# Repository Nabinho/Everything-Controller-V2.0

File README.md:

# Everything Controller V2.0

This project is an updated version of my Everything Controller I did a while back. This time I focused on transmission time, using the powerfull Teensy 3.2 as the main microcontroller. I also added more inputs, so I have even more functions to help the control of various projects, and not only robots.

The PCB and base code of this project are available for replication. The Teensy 3.2 is discontinued, so if you don't have one, maybe this can be a great reference for your own project.

## BOM

The SMD components list can be found in the interactive BOM generated with the KiCad project. Besides the Teensy 3.2 I had for a while, the rest of the THT components I bought from Aliexpress and all of the links are listed below.

* 1x - [EByte E01](https://pt.aliexpress.com/item/1005001803228202.html?spm=a2g0o.order_list.order_list_main.110.3876caa4MgzPN5&gatewayAdapt=glo2bra);
* 1x - [Waveshare SSD1327 128x128 OLED Display](https://pt.aliexpress.com/item/32853228170.html?spm=a2g0o.order_list.order_list_main.22.3876caa4MgzPN5&gatewayAdapt=glo2bra);
* 2x - [10k Ohm Rotary Potentiometer](https://pt.aliexpress.com/item/1005005956593595.html?spm=a2g0o.order_list.order_list_main.34.3876caa4MgzPN5&gatewayAdapt=glo2bra);
* 2x - [10k Ohm Slider Potentiometer](https://pt.aliexpress.com/item/1005006075347058.html?spm=a2g0o.order_list.order_list_main.35.3876caa4MgzPN5&gatewayAdapt=glo2bra);
* 2x - [EC11 Rotary Encoder](https://pt.aliexpress.com/item/1005005882895811.html?spm=a2g0o.order_list.order_list_main.36.3876caa4MgzPN5&gatewayAdapt=glo2bra);
* 4x - [Cherry MX Switches (any color)](https://pt.aliexpress.com/item/1005006255961111.html?spm=a2g0o.cart.0.0.360c7f06wTXtF8&mp=1&gatewayAdapt=glo2bra);
* 2x - [PS5 Hall Effect Joystick](https://pt.aliexpress.com/item/1005006165745072.html?spm=a2g0o.order_list.order_list_main.58.3876caa4MgzPN5&gatewayAdapt=glo2bra);

Besides the electronics components, a pair of 18650 Li-Ion batteries is necessary to power the controller.

Some screws and nuts ares also recommended to mount the soldered PCB in an acrylic or 3D printed backplate.

## Bechmark Tests

As soon as the controller was finished I ran some benchmark tests to validate the controller performance. Bellow are the tests I ran so far and the results.

| Tests | Results |
| ------------- |:-------------:|
| Battery feedback reading | The battery feedback circuit from the controller had a precision of 0.3 mV most of the time, but I had to include a "debounce" for the OLED update, due to some voltage fluctuation |
| Transmission latency | With a simple receiver just connected to the NRF24L01 transceiver and only calculating the time between messages (data sent and acknolegement) the average time was 3 ms during an 1 hour test |
| Battery duration | Using a pair of 3000 mAh 18650 Li-Ion batteries the controller stayed turned on during 21 hours (average consumption of 150 mA) |
| Transmission range | This test is still TBD, however I want to see if the optimistic expectations from EByte of a transmission range of 5 km is true |

### Conclusion/Contact

As this is a personal project, I would love to see if anyone replicate or takes inspiration from this project. So if you replicate or use this as a base for your own project, please share it with me in Instagram.

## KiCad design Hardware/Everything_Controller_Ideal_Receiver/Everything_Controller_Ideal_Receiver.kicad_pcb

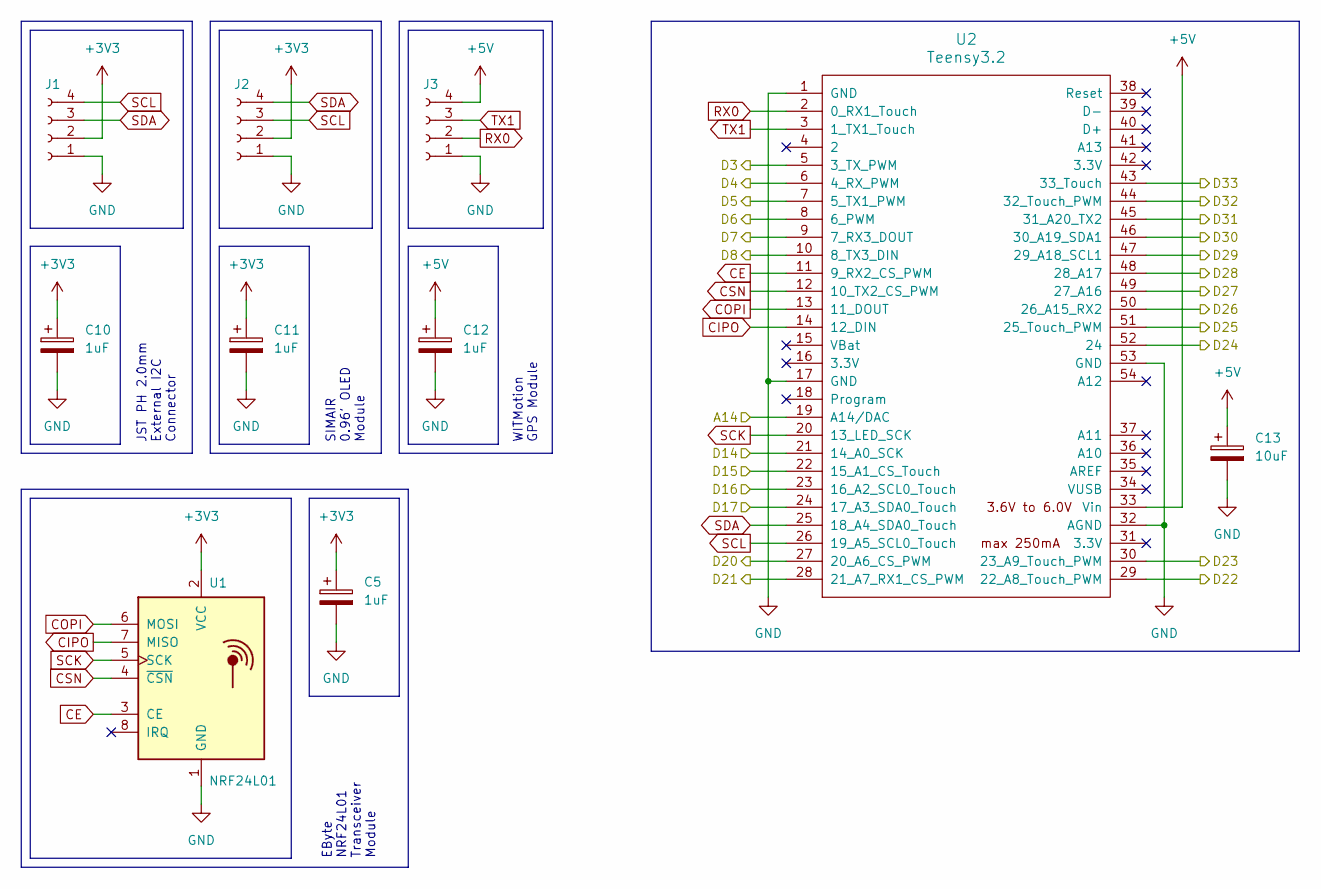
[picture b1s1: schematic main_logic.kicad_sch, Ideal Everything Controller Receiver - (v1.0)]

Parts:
C5, C10, C11, C12: 1uF; CP_EIA-3216-18_Kemet-A
C13: 10uF; CP_EIA-3528-21_Kemet-B
J1: Conn_01x04_Socket; JST_PH_S4B-PH-K_1x04_P2.00mm_Horizontal
J2: Conn_01x04_Socket; SIMAIR_OLED
J3: Conn_01x04_Socket; WitMotion_NMEA0183
U1: NRF24L01; EByte_NRF24L01_Breakout
U2: Teensy3.2; Teensy_3.2

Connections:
+3V3: C5.1, C10.1, C11.1, J1.2, J2.2, U1.2 (VCC); also elsewhere on the board
+5V: C12.1, C13.1, J3.4, U2.33 (Vin); also elsewhere on the board
/Inputs and Outputs/BOTAO1: U2.21 (14_A0_SCK); also elsewhere on the board
/Inputs and Outputs/BOTAO2: U2.22 (15_A1_CS_Touch); also elsewhere on the board
/Inputs and Outputs/BOTAO3: U2.23 (16_A2_SCL0_Touch); also elsewhere on the board
/Inputs and Outputs/BOTAO4: U2.24 (17_A3_SDA0_Touch); also elsewhere on the board
/Inputs and Outputs/DOUT1: U2.47 (29_A18_SCL1); also elsewhere on the board
/Inputs and Outputs/DOUT2: U2.46 (30_A19_SDA1); also elsewhere on the board
/Inputs and Outputs/DOUT3: U2.45 (31_A20_TX2); also elsewhere on the board
/Inputs and Outputs/DOUT4: U2.48 (28_A17); also elsewhere on the board
/Inputs and Outputs/DOUT5: U2.49 (27_A16); also elsewhere on the board
/Inputs and Outputs/DOUT6: U2.50 (26_A15_RX2); also elsewhere on the board
/Inputs and Outputs/DOUT7: U2.51 (25_Touch_PWM); also elsewhere on the board
/Inputs and Outputs/DOUT8: U2.52 (24); also elsewhere on the board
/Inputs and Outputs/LED1: U2.44 (32_Touch_PWM); also elsewhere on the board
/Inputs and Outputs/LED2: U2.43 (33_Touch); also elsewhere on the board
/Inputs and Outputs/PPM1: U2.29 (22_A8_Touch_PWM); also elsewhere on the board
/Inputs and Outputs/PPM2: U2.30 (23_A9_Touch_PWM); also elsewhere on the board
/Inputs and Outputs/PWM1: U2.10 (8_TX3_DIN); also elsewhere on the board
/Inputs and Outputs/PWM2: U2.9 (7_RX3_DOUT); also elsewhere on the board
/Inputs and Outputs/PWM3: U2.8 (6_PWM); also elsewhere on the board
/Inputs and Outputs/PWM4: U2.7 (5_TX1_PWM); also elsewhere on the board
/Inputs and Outputs/PWM5: U2.6 (4_RX_PWM); also elsewhere on the board
/Inputs and Outputs/PWM6: U2.5 (3_TX_PWM); also elsewhere on the board
/Inputs and Outputs/PWM7: U2.27 (20_A6_CS_PWM); also elsewhere on the board
/Inputs and Outputs/PWM8: U2.28 (21_A7_RX1_CS_PWM); also elsewhere on the board
/Main Logic/A14: U2.19 (A14/DAC); also elsewhere on the board
CE: U1.3 (CE), U2.11 (9_RX2_CS_PWM)
CIPO: U1.7 (MISO), U2.14 (12_DIN)
COPI: U1.6 (MOSI), U2.13 (11_DOUT)
CSN: U1.4 (~CSN), U2.12 (10_TX2_CS_PWM)
GND: C5.2, C10.2, C11.2, C12.2, C13.2, J1.1, J2.1, J3.1, U1.1 (GND), U2.1 (GND), U2.17 (GND), U2.32 (AGND), U2.53 (GND); also elsewhere on the board
RX0: J3.2, U2.2 (0_RX1_Touch)
SCK: U1.5 (SCK), U2.20 (13_LED_SCK)
SCL: J1.4, J2.3, U2.26 (19_A5_SCL0_Touch)
SDA: J1.3, J2.4, U2.25 (18_A4_SDA0_Touch)
TX1: J3.3, U2.3 (1_TX1_Touch)

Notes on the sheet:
SIMAIR 0.96' OLED Module
WITMotion GPS Module
JST PH 2.0mm External I2C Connector
EByte NRF24L01 Transceiver Module

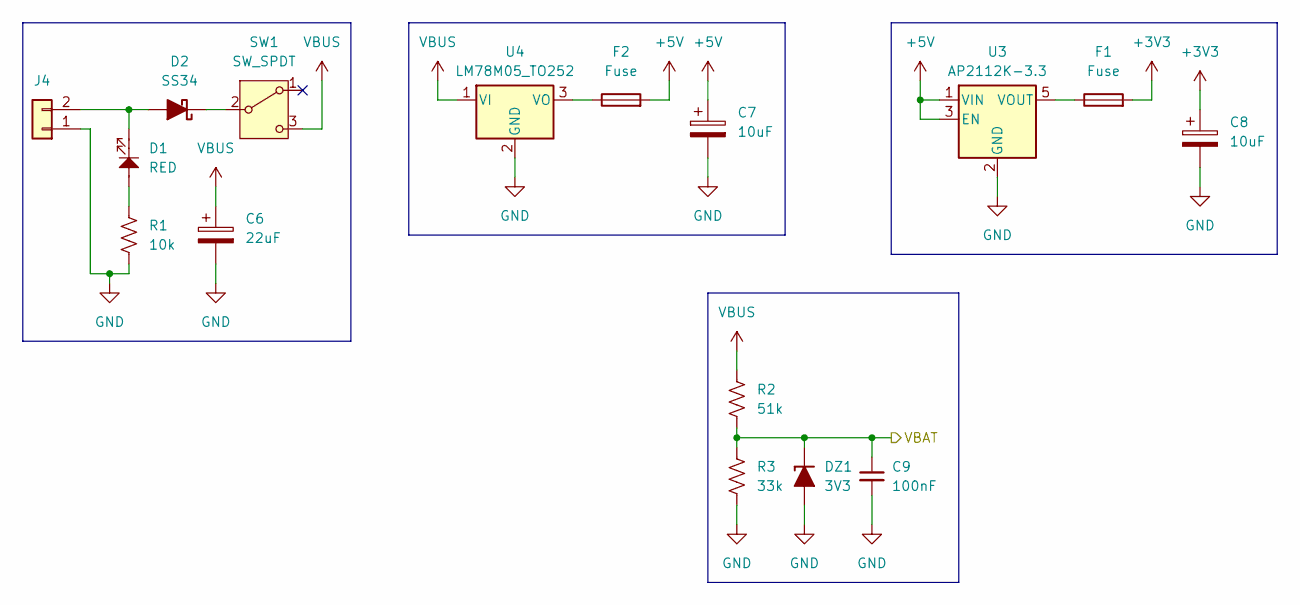
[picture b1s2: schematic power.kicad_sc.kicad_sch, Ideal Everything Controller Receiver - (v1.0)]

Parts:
C6: 22uF; CP_EIA-7343-31_Kemet-D
C7, C8: 10uF; CP_EIA-3528-21_Kemet-B
C9: 100nF; C_0805_2012Metric
D1: RED; LED_0805_2012Metric
D2: SS34; D_SMA
DZ1: 3V3; D_MiniMELF
F1: Fuse; Fuse_0805_2012Metric
F2: Fuse; Fuse_1812_4532Metric
J4: Conn_01x02; TerminalBlock_4Ucon_1x02_P3.50mm_Horizontal
R1: 10k; R_0805_2012Metric
R2: 51k; R_0805_2012Metric
R3: 33k; R_0805_2012Metric
SW1: SW_SPDT; SW_Slide_SPDT_Straight_CK_OS102011MS2Q
U3: AP2112K-3.3; SOT-23-5
U4: LM78M05_TO252; TO-252-2

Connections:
+3V3: C8.1, F1.2; also elsewhere on the board
+5V: C7.1, F2.2, U3.1 (VIN), U3.3 (EN); also elsewhere on the board
/Main Logic/A14: C9.1, DZ1.1 (K), R2.2, R3.1; also elsewhere on the board
GND: C6.2, C7.2, C8.2, C9.2, DZ1.2 (A), J4.1, R1.2, R3.2, U3.2 (GND), U4.2 (GND); also elsewhere on the board
unnamed: D1.2, R1.1
unnamed: D1.1, D2.2 (A), J4.2
unnamed: D2.1 (K), SW1.2 (B)
unnamed: F1.1, U3.5 (VOUT)
unnamed: F2.1, U4.3 (VO)
VBUS: C6.1, R2.1, SW1.3 (C), U4.1 (VI)

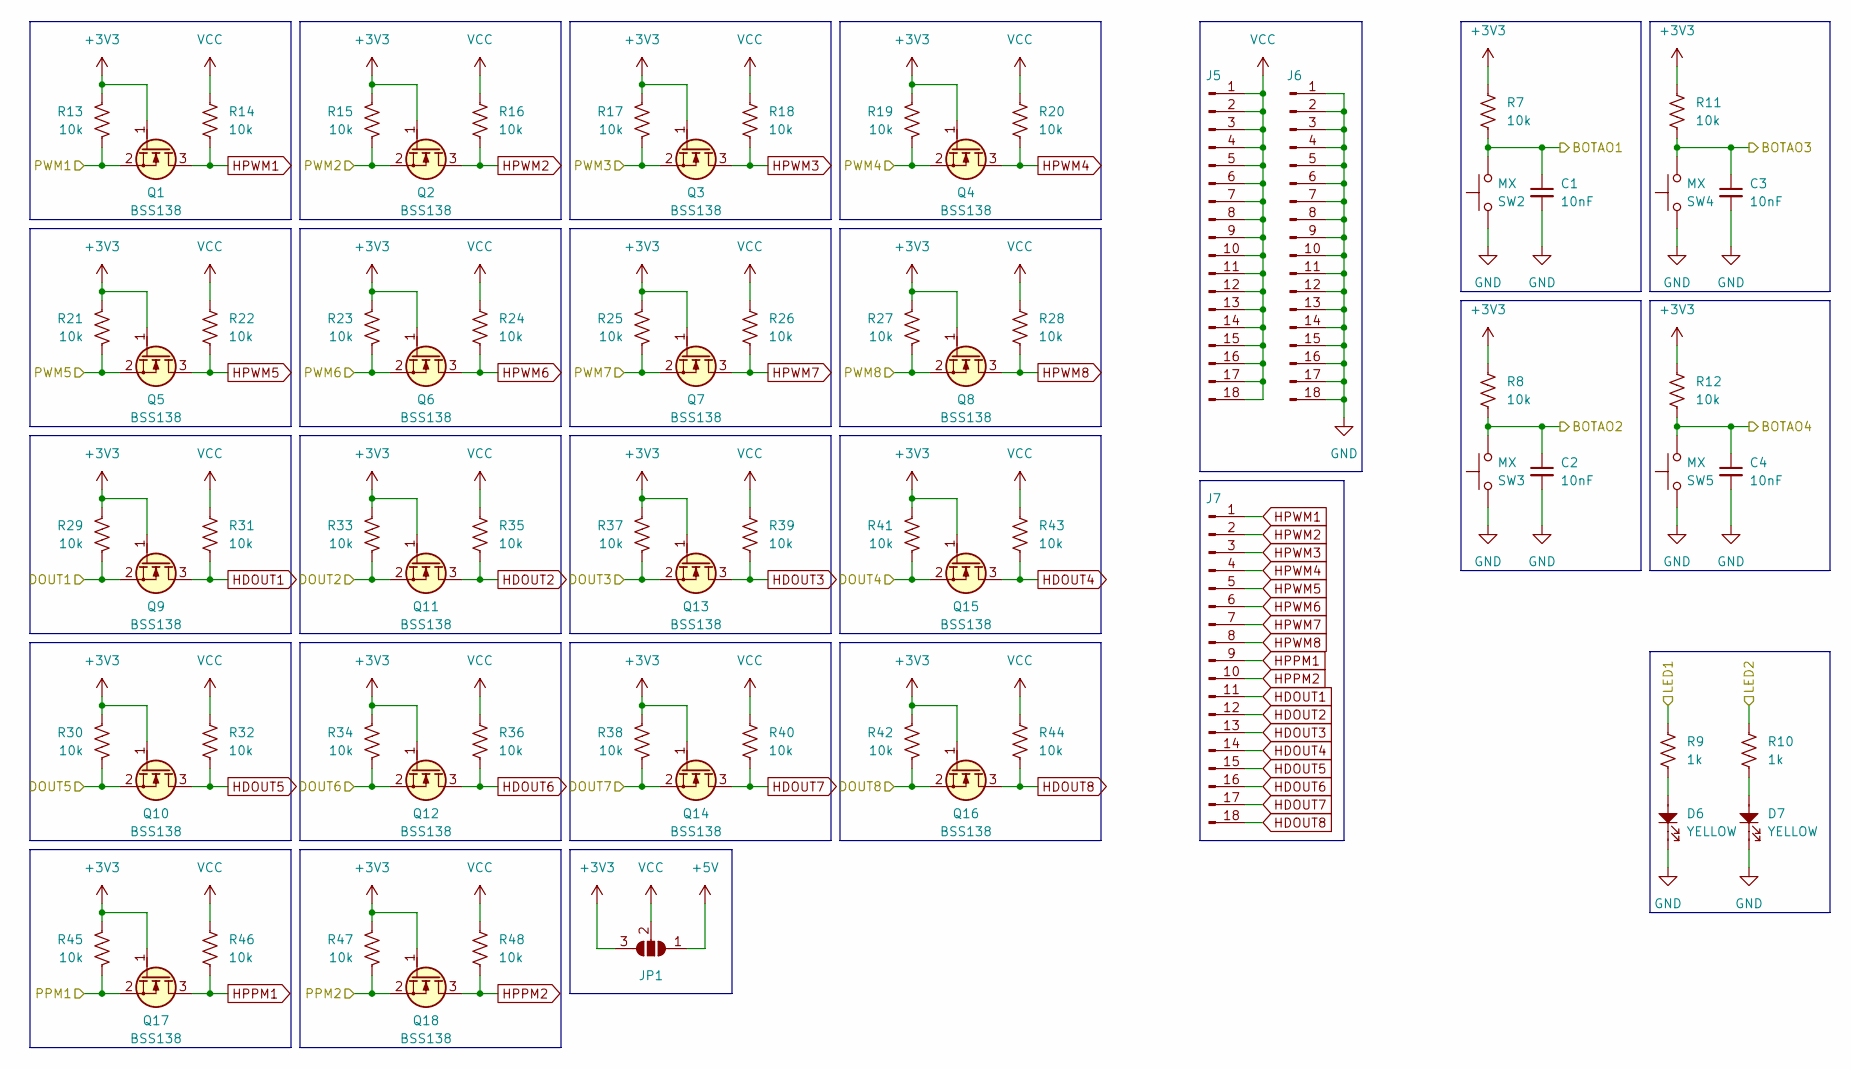
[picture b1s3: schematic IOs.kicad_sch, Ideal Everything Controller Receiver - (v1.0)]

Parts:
C1, C2, C3, C4: 10nF; C_0805_2012Metric
D6, D7: YELLOW; LED_0805_2012Metric
J5, J6, J7: Conn_01x18_Pin; PinHeader_1x18_P2.54mm_Vertical
JP1: SolderJumper_3_Open; SolderJumper-3_P1.3mm_Open_RoundedPad1.0x1.5mm
Q1, Q2, Q3, Q4, Q5, Q6, Q7, Q8, Q9, Q10, Q11, Q12, Q13, Q14, Q15, Q16, Q17, Q18: BSS138; SOT-23
R7, R8, R11, R12, R13, R14, R15, R16, R17, R18, R19, R20, R21, R22, R23, R24, R25, R26, R27, R28, R29, R30, R31, R32, R33, R34, R35, R36, R37, R38, R39, R40, R41, R42, R43, R44, R45, R46, R47, R48: 10k; R_0805_2012Metric
R9, R10: 1k; R_0805_2012Metric
SW2, SW3, SW4, SW5: MX; SW_Cherry_MX_PCB_1.00u

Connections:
+3V3: JP1.3 (B), Q1.1 (G), Q2.1 (G), Q3.1 (G), Q4.1 (G), Q5.1 (G), Q6.1 (G), Q7.1 (G), Q8.1 (G), Q9.1 (G), Q10.1 (G), Q11.1 (G), Q12.1 (G), Q13.1 (G), Q14.1 (G), Q15.1 (G), Q16.1 (G), Q17.1 (G), Q18.1 (G), R7.1, R8.1, R11.1, R12.1, R13.1, R15.1, R17.1, R19.1, R21.1, R23.1, R25.1, R27.1, R29.1, R30.1, R33.1, R34.1, R37.1, R38.1, R41.1, R42.1, R45.1, R47.1; also elsewhere on the board
+5V: JP1.1 (A); also elsewhere on the board
/Inputs and Outputs/BOTAO1: C1.1, R7.2, SW2.1; also elsewhere on the board
/Inputs and Outputs/BOTAO2: C2.1, R8.2, SW3.1; also elsewhere on the board
/Inputs and Outputs/BOTAO3: C3.1, R11.2, SW4.1; also elsewhere on the board
/Inputs and Outputs/BOTAO4: C4.1, R12.2, SW5.1; also elsewhere on the board
/Inputs and Outputs/DOUT1: Q9.2 (S), R29.2; also elsewhere on the board
/Inputs and Outputs/DOUT2: Q11.2 (S), R33.2; also elsewhere on the board
/Inputs and Outputs/DOUT3: Q13.2 (S), R37.2; also elsewhere on the board
/Inputs and Outputs/DOUT4: Q15.2 (S), R41.2; also elsewhere on the board
/Inputs and Outputs/DOUT5: Q10.2 (S), R30.2; also elsewhere on the board
/Inputs and Outputs/DOUT6: Q12.2 (S), R34.2; also elsewhere on the board
/Inputs and Outputs/DOUT7: Q14.2 (S), R38.2; also elsewhere on the board
/Inputs and Outputs/DOUT8: Q16.2 (S), R42.2; also elsewhere on the board
/Inputs and Outputs/LED1: R9.1; also elsewhere on the board
/Inputs and Outputs/LED2: R10.1; also elsewhere on the board
/Inputs and Outputs/PPM1: Q17.2 (S), R45.2; also elsewhere on the board
/Inputs and Outputs/PPM2: Q18.2 (S), R47.2; also elsewhere on the board
/Inputs and Outputs/PWM1: Q1.2 (S), R13.2; also elsewhere on the board
/Inputs and Outputs/PWM2: Q2.2 (S), R15.2; also elsewhere on the board
/Inputs and Outputs/PWM3: Q3.2 (S), R17.2; also elsewhere on the board
/Inputs and Outputs/PWM4: Q4.2 (S), R19.2; also elsewhere on the board
/Inputs and Outputs/PWM5: Q5.2 (S), R21.2; also elsewhere on the board
/Inputs and Outputs/PWM6: Q6.2 (S), R23.2; also elsewhere on the board
/Inputs and Outputs/PWM7: Q7.2 (S), R25.2; also elsewhere on the board
/Inputs and Outputs/PWM8: Q8.2 (S), R27.2; also elsewhere on the board
GND: C1.2, C2.2, C3.2, C4.2, D6.1, D7.1, J6.1, J6.2, J6.3, J6.4, J6.5, J6.6, J6.7, J6.8, J6.9, J6.10, J6.11, J6.12, J6.13, J6.14, J6.15, J6.16, J6.17, J6.18, SW2.2, SW3.2, SW4.2, SW5.2; also elsewhere on the board
HDOUT1: J7.11, Q9.3 (D), R31.2
HDOUT2: J7.12, Q11.3 (D), R35.2
HDOUT3: J7.13, Q13.3 (D), R39.2
HDOUT4: J7.14, Q15.3 (D), R43.2
HDOUT5: J7.15, Q10.3 (D), R32.2
HDOUT6: J7.16, Q12.3 (D), R36.2
HDOUT7: J7.17, Q14.3 (D), R40.2
HDOUT8: J7.18, Q16.3 (D), R44.2
HPPM1: J7.9, Q17.3 (D), R46.2
HPPM2: J7.10, Q18.3 (D), R48.2
HPWM1: J7.1, Q1.3 (D), R14.2
HPWM2: J7.2, Q2.3 (D), R16.2
HPWM3: J7.3, Q3.3 (D), R18.2
HPWM4: J7.4, Q4.3 (D), R20.2
HPWM5: J7.5, Q5.3 (D), R22.2
HPWM6: J7.6, Q6.3 (D), R24.2
HPWM7: J7.7, Q7.3 (D), R26.2
HPWM8: J7.8, Q8.3 (D), R28.2
unnamed: D6.2, R9.2
unnamed: D7.2, R10.2
VCC: J5.1, J5.2, J5.3, J5.4, J5.5, J5.6, J5.7, J5.8, J5.9, J5.10, J5.11, J5.12, J5.13, J5.14, J5.15, J5.16, J5.17, J5.18, JP1.2 (C), R14.1, R16.1, R18.1, R20.1, R22.1, R24.1, R26.1, R28.1, R31.1, R32.1, R35.1, R36.1, R39.1, R40.1, R43.1, R44.1, R46.1, R48.1

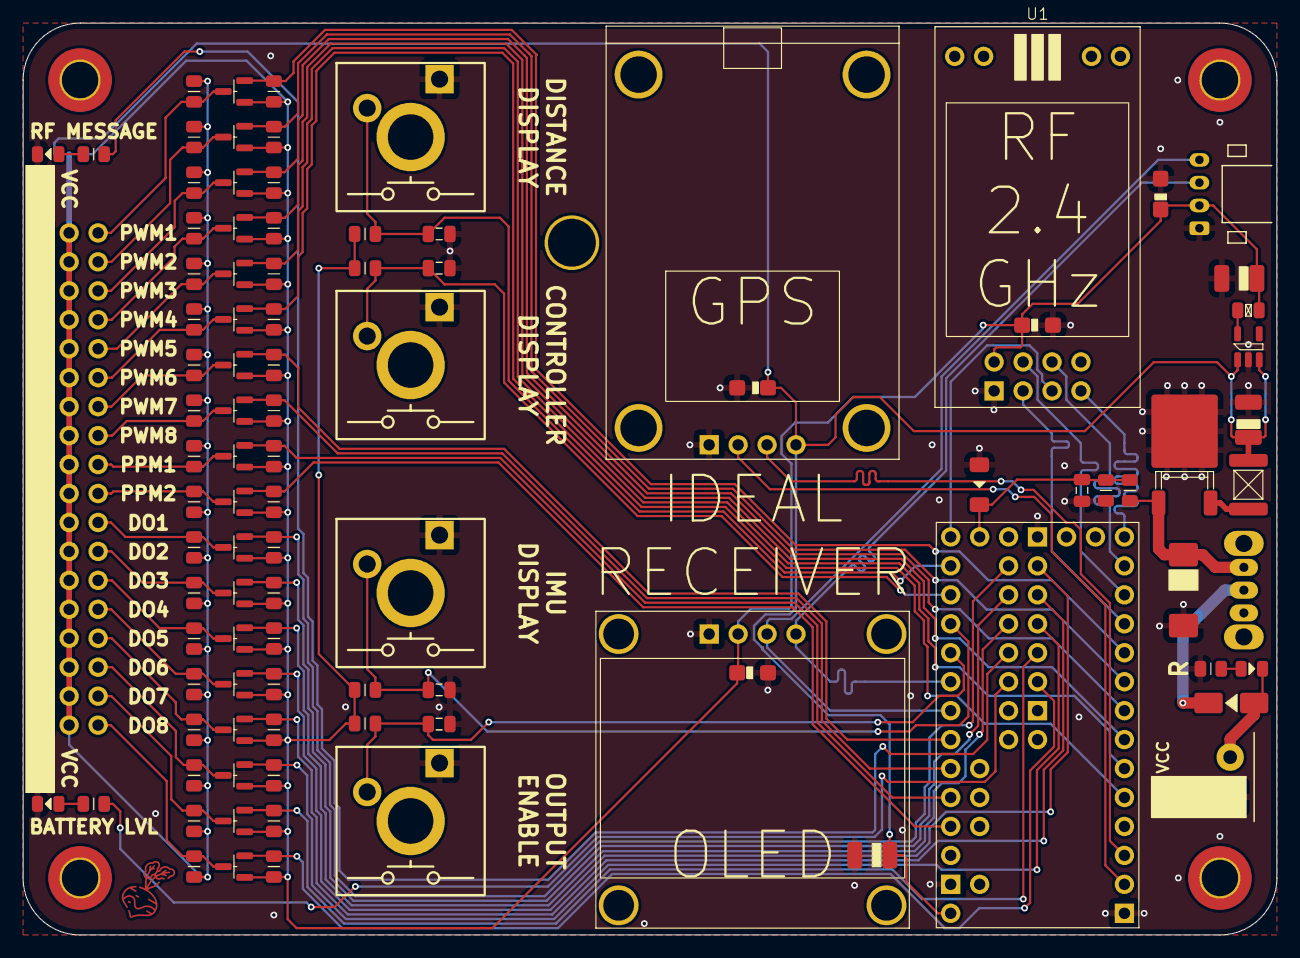
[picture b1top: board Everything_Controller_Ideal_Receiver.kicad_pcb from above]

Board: 2 copper layers, 110.0 x 80.0 mm, 100 parts (1 on the bottom side), 64 nets.

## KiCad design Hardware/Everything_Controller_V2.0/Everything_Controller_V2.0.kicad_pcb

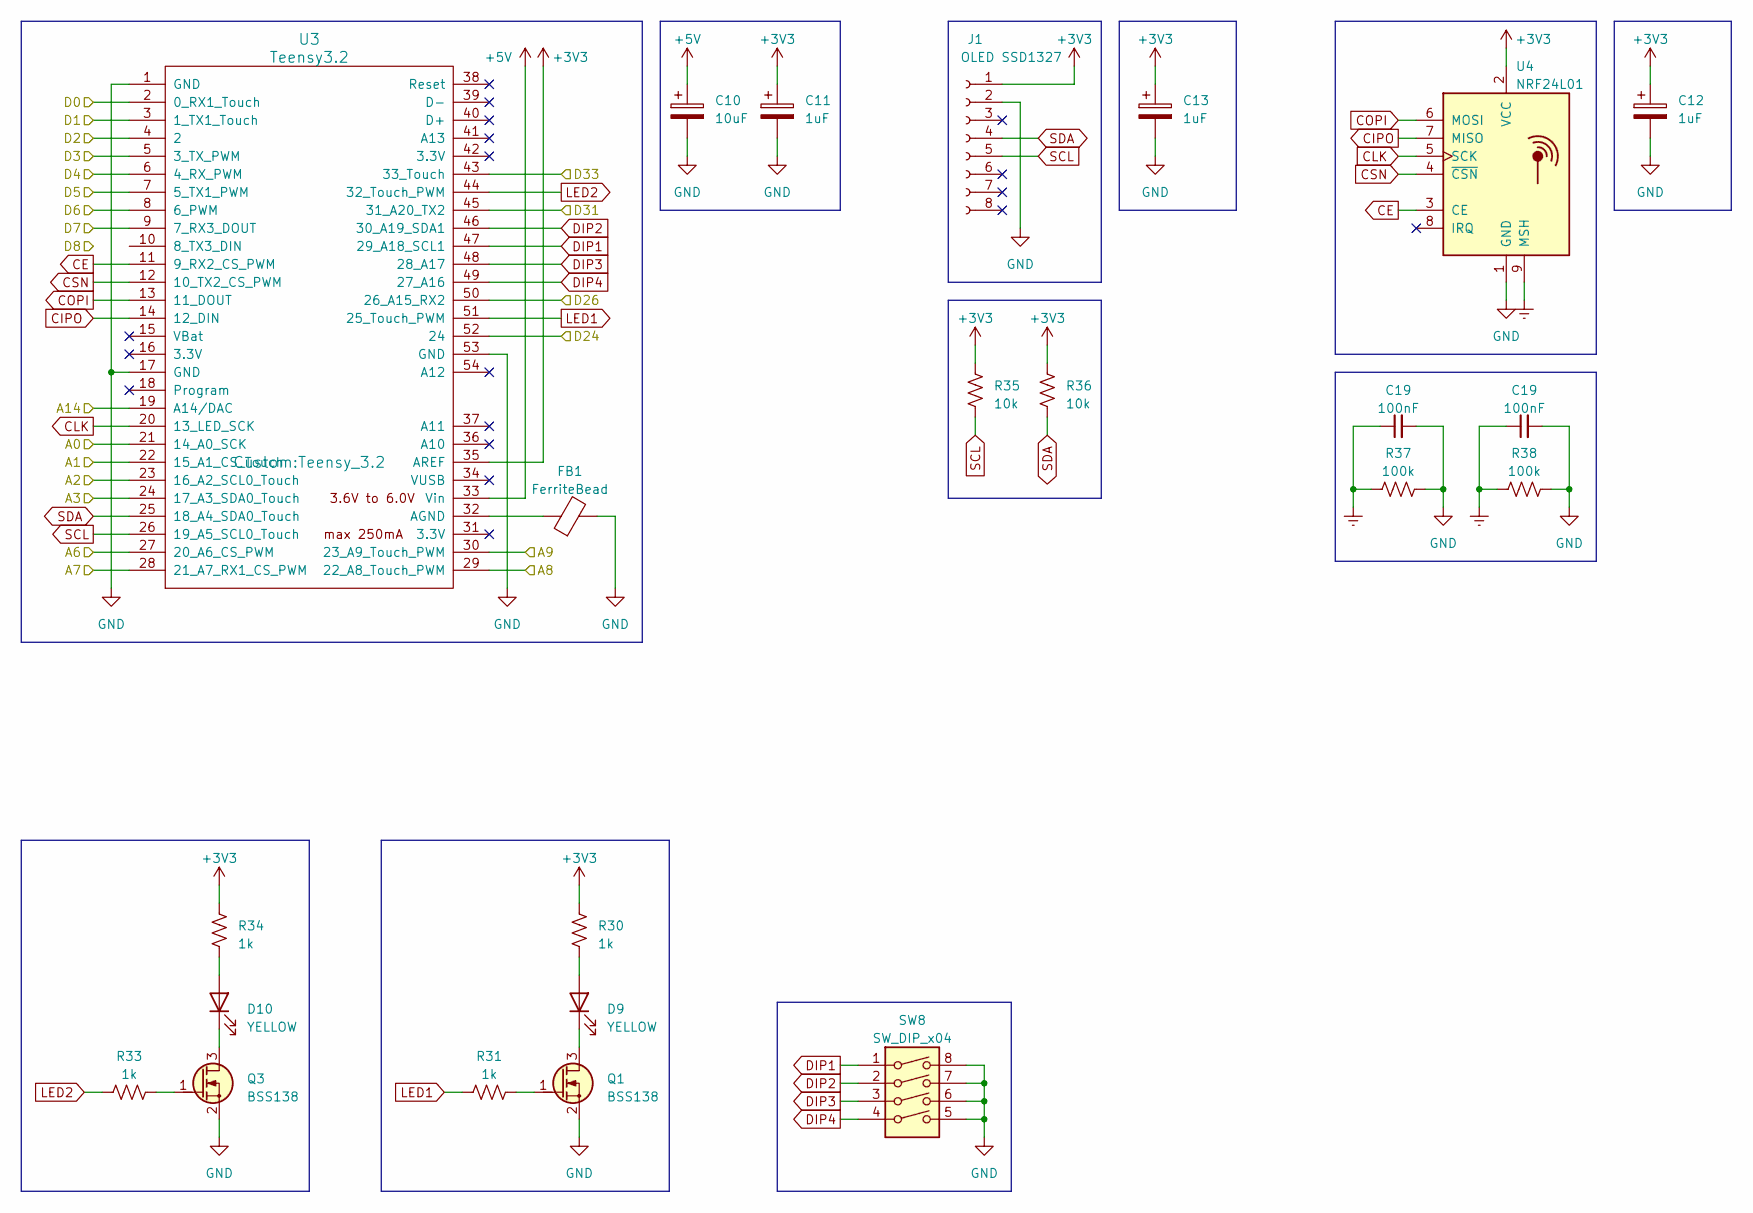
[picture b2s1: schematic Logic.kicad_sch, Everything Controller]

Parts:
C10: 10uF; CP_EIA-3216-18_Kemet-A
C11, C12, C13: 1uF; CP_EIA-3216-18_Kemet-A
C19: 100nF; C_0805_2012Metric
D9, D10: YELLOW; LED_0805_2012Metric
FB1: FerriteBead; L_0805_2012Metric
J1: OLED SSD1327; SSD1327_Breakout
Q1, Q3: BSS138; SOT-23
R30, R31, R33, R34: 1k; R_0805_2012Metric
R35, R36: 10k; R_0805_2012Metric
R37, R38: 100k; R_0805_2012Metric
SW8: SW_DIP_x04; SW_DIP_SPSTx04_Slide_Omron_A6S-410x_W8.9mm_P2.54mm
U3: Teensy3.2; Teensy_3.2
U4: NRF24L01; EByte_NRF24L01_Breakout

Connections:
+3V3: C11.1, C12.1, C13.1, J1.1, R30.1, R34.1, R35.1, R36.1, U3.35 (AREF), U4.2 (VCC); also elsewhere on the board
+5V: C10.1, U3.33 (Vin); also elsewhere on the board
/Inputs/BT1: U3.45 (31_A20_TX2); also elsewhere on the board
/Inputs/BT2: U3.52 (24); also elsewhere on the board
/Inputs/BT3: U3.50 (26_A15_RX2); also elsewhere on the board
/Inputs/BT4: U3.43 (33_Touch); also elsewhere on the board
/Inputs/CLK1: U3.9 (7_RX3_DOUT); also elsewhere on the board
/Inputs/CLK2: U3.6 (4_RX_PWM); also elsewhere on the board
/Inputs/DT1: U3.8 (6_PWM); also elsewhere on the board
/Inputs/DT2: U3.7 (5_TX1_PWM); also elsewhere on the board
/Inputs/E_BT1: U3.5 (3_TX_PWM); also elsewhere on the board
/Inputs/E_BT2: U3.4 (2); also elsewhere on the board
/Inputs/J_BT1: U3.2 (0_RX1_Touch); also elsewhere on the board
/Inputs/J_BT2: U3.3 (1_TX1_Touch); also elsewhere on the board
/Inputs/POT1: U3.22 (15_A1_CS_Touch); also elsewhere on the board
/Inputs/POT3: U3.23 (16_A2_SCL0_Touch); also elsewhere on the board
/Inputs/POT4: U3.21 (14_A0_SCK); also elsewhere on the board
/Inputs/X_AX1: U3.27 (20_A6_CS_PWM); also elsewhere on the board
/Inputs/X_AX2: U3.30 (23_A9_Touch_PWM); also elsewhere on the board
/Inputs/Y_AX1: U3.28 (21_A7_RX1_CS_PWM); also elsewhere on the board
/Inputs/Y_AX2: U3.29 (22_A8_Touch_PWM); also elsewhere on the board
/Logic/A14: U3.19 (A14/DAC); also elsewhere on the board
CE: U3.11 (9_RX2_CS_PWM), U4.3 (CE)
CIPO: U3.14 (12_DIN), U4.7 (MISO)
CLK: U3.20 (13_LED_SCK), U4.5 (SCK)
COPI: U3.13 (11_DOUT), U4.6 (MOSI)
CSN: U3.12 (10_TX2_CS_PWM), U4.4 (~CSN)
DIP1: SW8.1, U3.47 (29_A18_SCL1)
DIP2: SW8.2, U3.46 (30_A19_SDA1)
DIP3: SW8.3, U3.48 (28_A17)
DIP4: SW8.4, U3.49 (27_A16)
GND: C10.2, C11.2, C12.2, C13.2, C19.2, FB1.2, J1.2, Q1.2 (S), Q3.2 (S), R37.2, R38.2, SW8.5, SW8.6, SW8.7, SW8.8, U3.1 (GND), U3.17 (GND), U3.53 (GND), U4.1 (GND); also elsewhere on the board
LED1: R31.1, U3.51 (25_Touch_PWM)
LED2: R33.1, U3.44 (32_Touch_PWM)
unnamed: D9.2 (A), R30.2
unnamed: D9.1 (K), Q1.3 (D)
unnamed: D10.2 (A), R34.2
unnamed: D10.1 (K), Q3.3 (D)
unnamed: Q1.1 (G), R31.2
unnamed: Q3.1 (G), R33.2
unnamed: FB1.1, U3.32 (AGND)
SCL: J1.5, R35.2, U3.26 (19_A5_SCL0_Touch)
SDA: J1.4, R36.2, U3.25 (18_A4_SDA0_Touch)

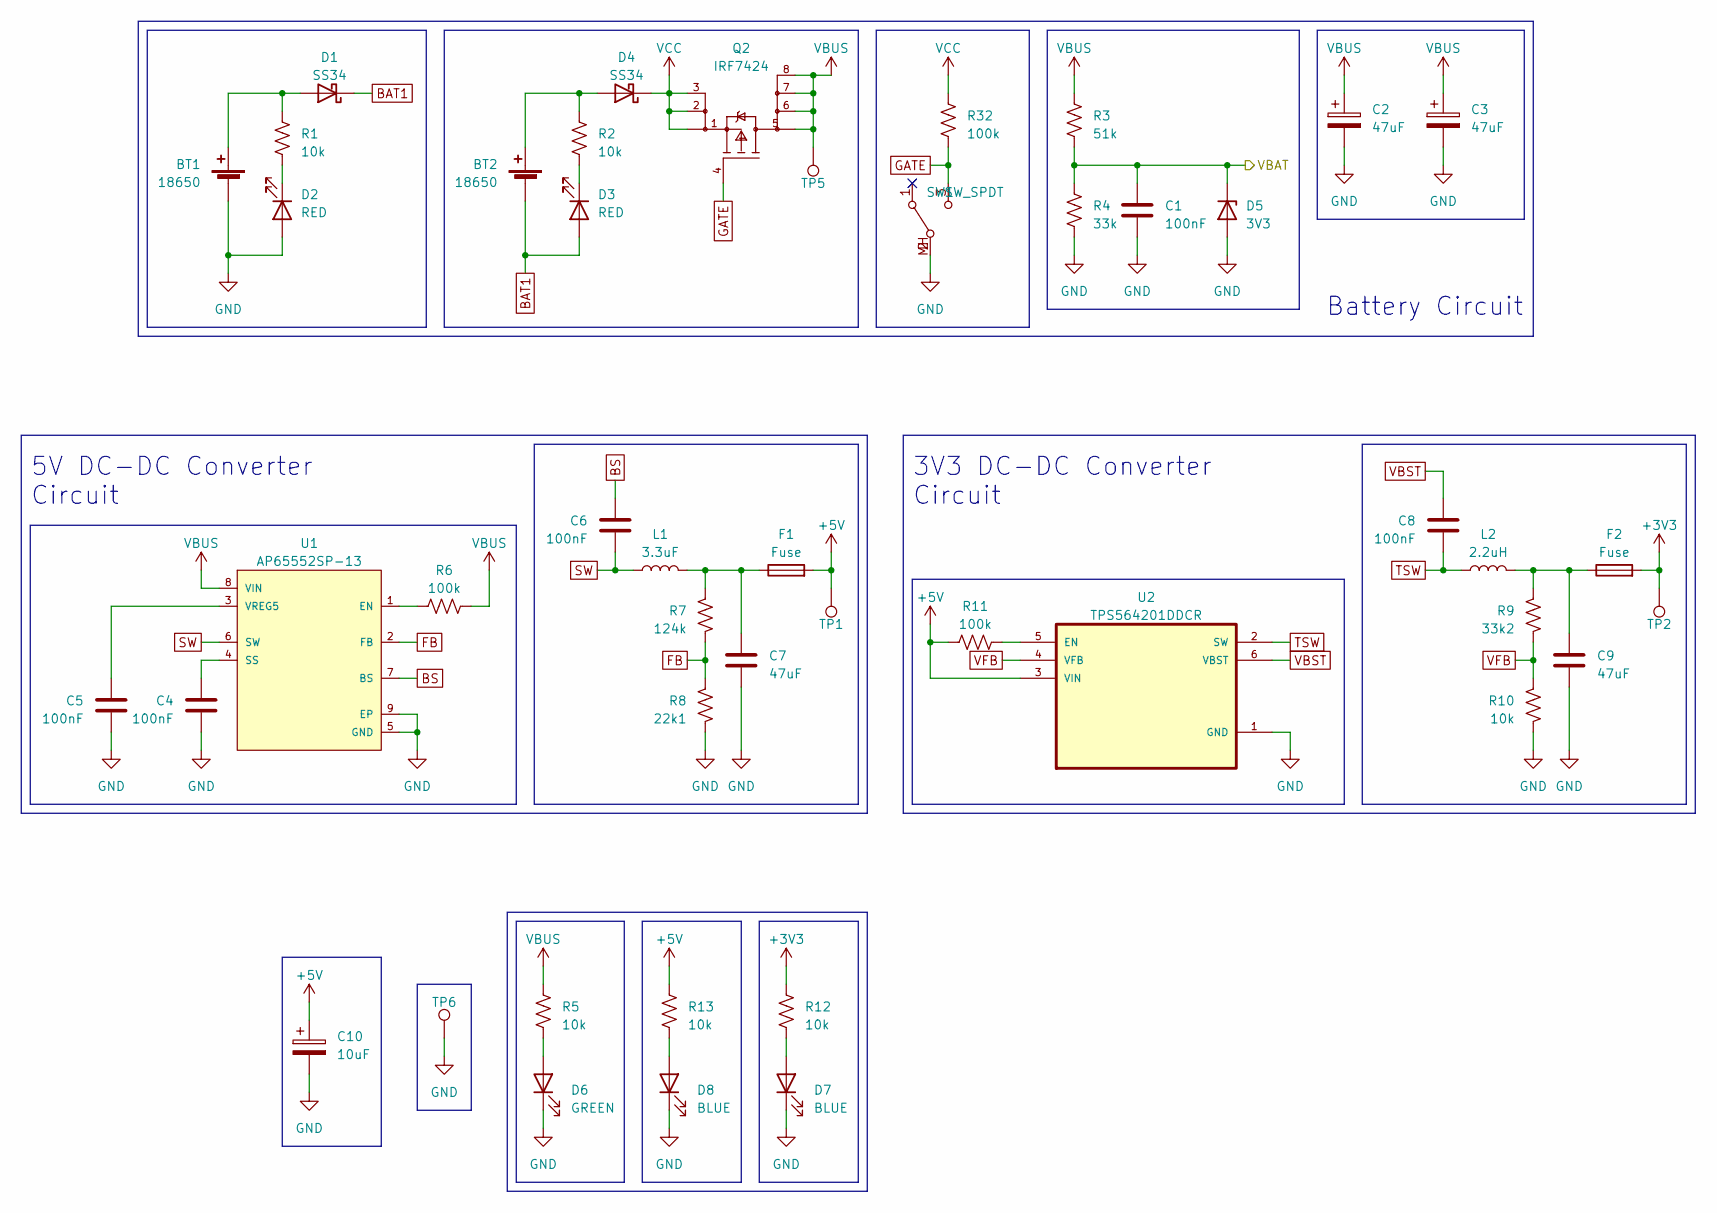
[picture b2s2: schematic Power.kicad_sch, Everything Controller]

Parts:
BT1, BT2: 18650; TerminalBlock_4Ucon_1x02_P3.50mm_Horizontal
C1, C4, C5, C6, C8: 100nF; C_0805_2012Metric
C2, C3: 47uF; CP_EIA-7343-31_Kemet-D
C7, C9: 47uF; C_1210_3225Metric
C10: 10uF; CP_EIA-3528-21_Kemet-B
D1, D4: SS34; D_SMA
D2, D3: RED; LED_0805_2012Metric
D5: 3V3; D_MiniMELF
D6: GREEN; LED_0805_2012Metric
D7, D8: BLUE; LED_0805_2012Metric
F1, F2: Fuse; Fuse_1206_3216Metric
L1: 3.3uF; L_1210_3225Metric
L2: 2.2uH; L_1210_3225Metric
Q2: IRF7424; Infineon-PG-DSO-8-11_2006-902-MFG
R1, R2, R5, R10, R12, R13: 10k; R_0805_2012Metric
R3: 51k; R_0805_2012Metric
R4: 33k; R_0805_2012Metric
R6, R11, R32: 100k; R_0805_2012Metric
R7: 124k; R_0805_2012Metric
R8: 22k1; R_0805_2012Metric
R9: 33k2; R_0805_2012Metric
SW1: SW_SPDT; SW_Slide_1P2T_CK_OS102011MS2Q
TP1, TP2, TP5, TP6: TestPoint; TestPoint_Pad_D1.5mm
U1: AP65552SP-13; Diodes-AP65552SP-13-06_2015-0-0
U2: TPS564201DDCR; Texas_Instruments-DDC_R-PDSO-G6-0-0-0

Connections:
+3V3: F2.2, R12.2, TP2.1; also elsewhere on the board
+5V: C10.1, F1.2, R11.2, R13.2, TP1.1, U2.3 (VIN); also elsewhere on the board
/Logic/A14: C1.1, D5.1 (K), R3.2, R4.1; also elsewhere on the board
BAT1: BT2.2 (-), D1.1 (K), D3.2 (A)
BS: C6.1, U1.7 (BS)
FB: R7.2, R8.1, U1.2 (FB)
GATE: Q2.4 (G), R32.2, SW1.3 (C)
GND: BT1.2 (-), C1.2, C2.2, C3.2, C4.2, C5.2, C7.2, C9.2, C10.2, D2.2 (A), D5.2 (A), D6.1 (K), D7.1 (K), D8.1 (K), R4.2, R8.2, R10.2, SW1.2 (B), SW1.MH (B), TP6.1, U1.5 (GND), U1.9 (EP), U2.1 (GND); also elsewhere on the board
unnamed: BT1.1 (+), D1.2 (A), R1.1
unnamed: BT2.1 (+), D4.2 (A), R2.1
unnamed: C7.1, F1.1, L1.2, R7.1
unnamed: C9.1, F2.1, L2.2, R9.1
unnamed: D2.1 (K), R1.2
unnamed: D3.1 (K), R2.2
unnamed: D6.2 (A), R5.1
unnamed: D7.2 (A), R12.1
unnamed: D8.2 (A), R13.1
unnamed: R6.2, U1.1 (EN)
unnamed: C4.1, U1.4 (SS)
unnamed: C5.1, U1.3 (VREG5)
unnamed: R11.1, U2.5 (EN)
SW: C6.2, L1.1, U1.6 (SW)
TSW: C8.2, L2.1, U2.2 (SW)
VBST: C8.1, U2.6 (VBST)
VBUS: C2.1, C3.1, Q2.5 (D), Q2.6 (D), Q2.7 (D), Q2.8 (D), R3.1, R5.2, R6.1, TP5.1, U1.8 (VIN)
VCC: D4.1 (K), Q2.1 (S), Q2.2 (S), Q2.3 (S), R32.1
VFB: R9.2, R10.1, U2.4 (VFB)

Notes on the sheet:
5V DC-DC Converter Circuit
Battery Circuit
3V3 DC-DC Converter Circuit

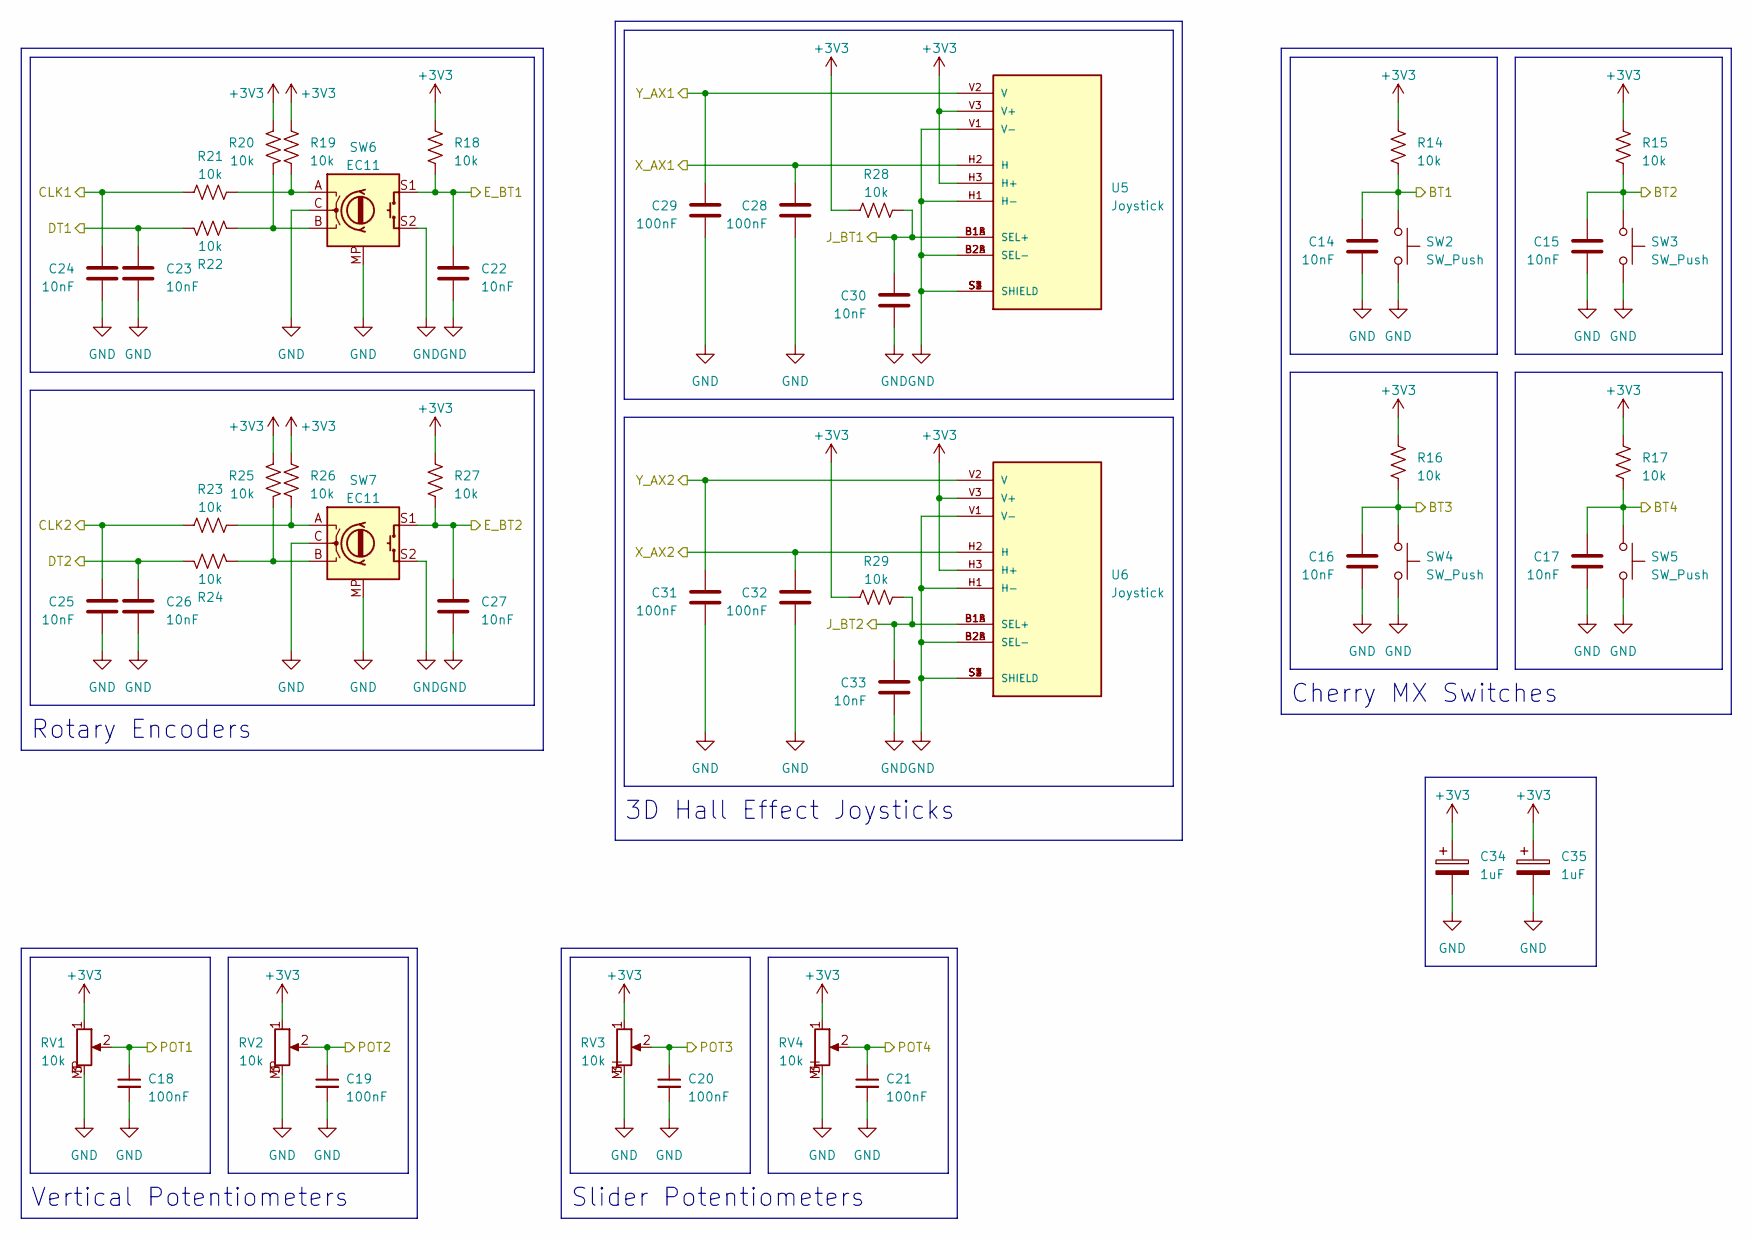
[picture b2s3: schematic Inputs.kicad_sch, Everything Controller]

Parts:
C14, C15, C16, C17, C22, C23, C24, C25, C26, C27, C30, C33: 10nF; C_0805_2012Metric
C18, C19, C20, C21, C28, C29, C31, C32: 100nF; C_0805_2012Metric
C34, C35: 1uF; CP_EIA-3216-18_Kemet-A
R14, R15, R16, R17, R18, R19, R20, R21, R22, R23, R24, R25, R26, R27, R28, R29: 10k; R_0805_2012Metric
RV1, RV2: 10k; Potentiometer_Alps_RK09K_Single_Vertical
RV3, RV4: 10k; RS30111A602N
SW2, SW3, SW4, SW5: SW_Push; SW_Cherry_MX_Plate
SW6, SW7: EC11; RotaryEncoder_Alps_EC11E_Vertical_H20mm
U5, U6: Joystick; XDCR_COM-09032

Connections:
+3V3: C34.1, C35.1, R14.1, R15.1, R16.1, R17.1, R18.1, R19.1, R20.1, R25.1, R26.1, R27.1, R28.1, R29.1, RV1.1, RV2.1, RV3.1, RV4.1, U5.H3 (H+), U5.V3 (V+), U6.H3 (H+), U6.V3 (V+); also elsewhere on the board
/Inputs/BT1: C14.1, R14.2, SW2.1; also elsewhere on the board
/Inputs/BT2: C15.1, R15.2, SW3.1; also elsewhere on the board
/Inputs/BT3: C16.1, R16.2, SW4.1; also elsewhere on the board
/Inputs/BT4: C17.1, R17.2, SW5.1; also elsewhere on the board
/Inputs/CLK1: C24.1, R21.1; also elsewhere on the board
/Inputs/CLK2: C25.1, R23.1; also elsewhere on the board
/Inputs/DT1: C23.1, R22.1; also elsewhere on the board
/Inputs/DT2: C26.1, R24.1; also elsewhere on the board
/Inputs/E_BT1: C22.1, R18.2, SW6.S1; also elsewhere on the board
/Inputs/E_BT2: C27.1, R27.2, SW7.S1; also elsewhere on the board
/Inputs/J_BT1: C30.1, R28.2, U5.B1A (SEL+), U5.B1B (SEL+); also elsewhere on the board
/Inputs/J_BT2: C33.1, R29.2, U6.B1A (SEL+), U6.B1B (SEL+); also elsewhere on the board
/Inputs/POT1: C18.1, RV1.2; also elsewhere on the board
/Inputs/POT3: C20.1, RV3.2; also elsewhere on the board
/Inputs/POT4: C21.1, RV4.2; also elsewhere on the board
/Inputs/X_AX1: C28.1, U5.H2 (H); also elsewhere on the board
/Inputs/X_AX2: C32.1, U6.H2 (H); also elsewhere on the board
/Inputs/Y_AX1: C29.1, U5.V2 (V); also elsewhere on the board
/Inputs/Y_AX2: C31.1, U6.V2 (V); also elsewhere on the board
GND: C14.2, C15.2, C16.2, C17.2, C18.2, C19.2, C20.2, C21.2, C22.2, C23.2, C24.2, C25.2, C26.2, C27.2, C28.2, C29.2, C30.2, C31.2, C32.2, C33.2, C34.2, C35.2, RV1.3, RV1.MP (3), RV2.3, RV2.MP (3), RV3.3, RV3.MH (3), RV4.3, RV4.MH (3), SW2.2, SW3.2, SW4.2, SW5.2, SW6.C, SW6.MP, SW6.S2, SW7.C, SW7.MP, SW7.S2, U5.B2A (SEL-), U5.B2B (SEL-), U5.H1 (H-), U5.S1 (SHIELD), U5.S2 (SHIELD), U5.S3 (SHIELD), U5.S4 (SHIELD), U5.V1 (V-), U6.B2A (SEL-), U6.B2B (SEL-), U6.H1 (H-), U6.S1 (SHIELD), U6.S2 (SHIELD), U6.S3 (SHIELD), U6.S4 (SHIELD), U6.V1 (V-); also elsewhere on the board
unnamed: R19.2, R21.2, SW6.A
unnamed: R20.2, R22.2, SW6.B
unnamed: R23.2, R26.2, SW7.A
unnamed: R24.2, R25.2, SW7.B

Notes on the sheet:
Slider Potentiometers
Cherry MX Switches
Vertical Potentiometers
Rotary Encoders
3D Hall Effect Joysticks

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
